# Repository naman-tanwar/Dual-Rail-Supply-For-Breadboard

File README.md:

# Dual-Rail-Supply-For-Breadboard
A Breadboard attachable Dual Rail power supply.
This circuit will provide +V, GND, and -V to the breadboard which is very useful for testing OP-AMP circuits. You can power this circuit with a 12V DC Jack and Micro USB Cable!
The Output voltage can be adjusted using the potentiometer provided. The max output voltage is around 27V (+13.5V and -13.5V). The Display shows the total output voltage.

# Project Image

# Circuit

# PCB

# 3D View

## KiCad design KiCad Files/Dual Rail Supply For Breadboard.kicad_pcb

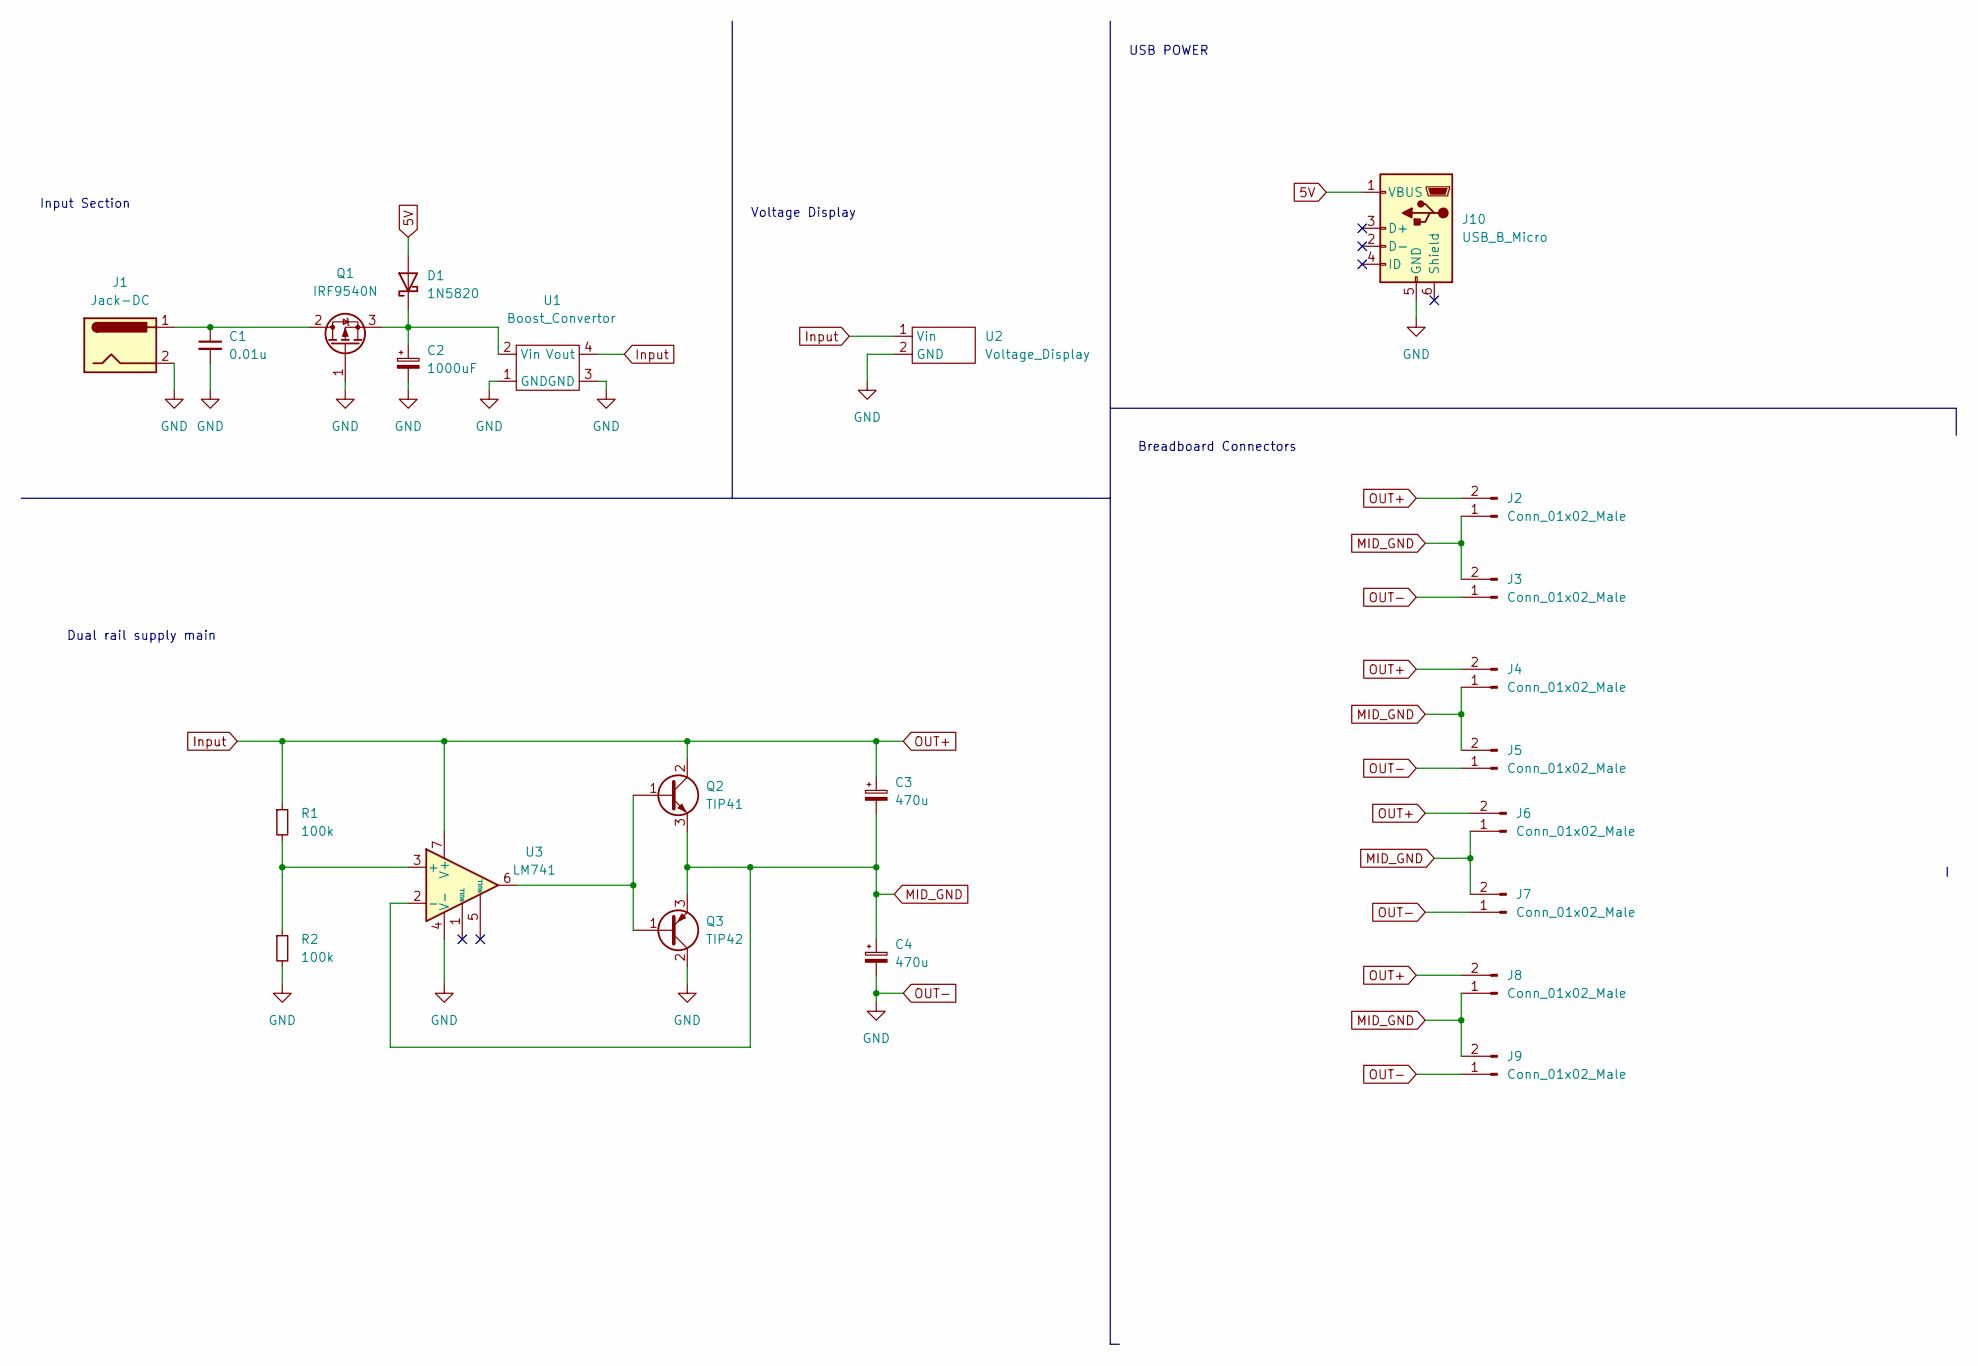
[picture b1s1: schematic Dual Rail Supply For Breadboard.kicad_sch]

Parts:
C1: 0.01u; C_Disc_D5.0mm_W2.5mm_P2.50mm
C2: 1000uF; CP_Radial_D12.5mm_P5.00mm
C3, C4: 470u; CP_Radial_D10.0mm_P5.00mm
D1: 1N5820; D_DO-201AD_P12.70mm_Horizontal
J1: Jack-DC; BarrelJack_Horizontal
J2, J3, J4, J5, J6, J7, J8, J9: Conn_01x02_Male; custom_PinHeader_1x02_P2.54mm_Vertical
J10: USB_B_Micro; USB_Micro-B_GCT_USB3076-30-A
Q1: IRF9540N; TO-220-3_Vertical
Q2: TIP41; TO-220-3_Vertical
Q3: TIP42; TO-220-3_Vertical
R1, R2: 100k; R_Axial_DIN0309_L9.0mm_D3.2mm_P12.70mm_Horizontal
U1: Boost_Convertor; MT3608 boost
U2: Voltage_Display; Voltage_disp_2wire
U3: LM741; DIP-8_W7.62mm_Socket_LongPads

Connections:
5V: D1.2 (A), J10.1 (VBUS)
Input: C3.1, J2.2, J4.2, J6.2, J8.2, Q2.2 (C), R1.1, U1.4 (Vout), U2.1 (Vin), U3.7 (V+)
MID_GND: C3.2, C4.1, J2.1, J3.2, J4.1, J5.2, J6.1, J7.2, J8.1, J9.2, Q2.3 (E), Q3.3 (E), U3.2 (-)
unnamed: C1.1, J1.1, Q1.2 (D)
unnamed: C2.1, D1.1 (K), Q1.3 (S), U1.2 (Vin)
unnamed: Q2.1 (B), Q3.1 (B), U3.6
unnamed: R1.2, R2.1, U3.3 (+)
OUT-: C1.2, C2.2, C4.2, J1.2, J3.1, J5.1, J7.1, J9.1, J10.5 (GND), Q1.1 (G), Q3.2 (C), R2.2, U1.1 (GND), U1.3 (GND), U2.2 (GND), U3.4 (V-)

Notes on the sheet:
Input Section
Dual rail supply main
Voltage Display
USB POWER
Breadboard Connectors

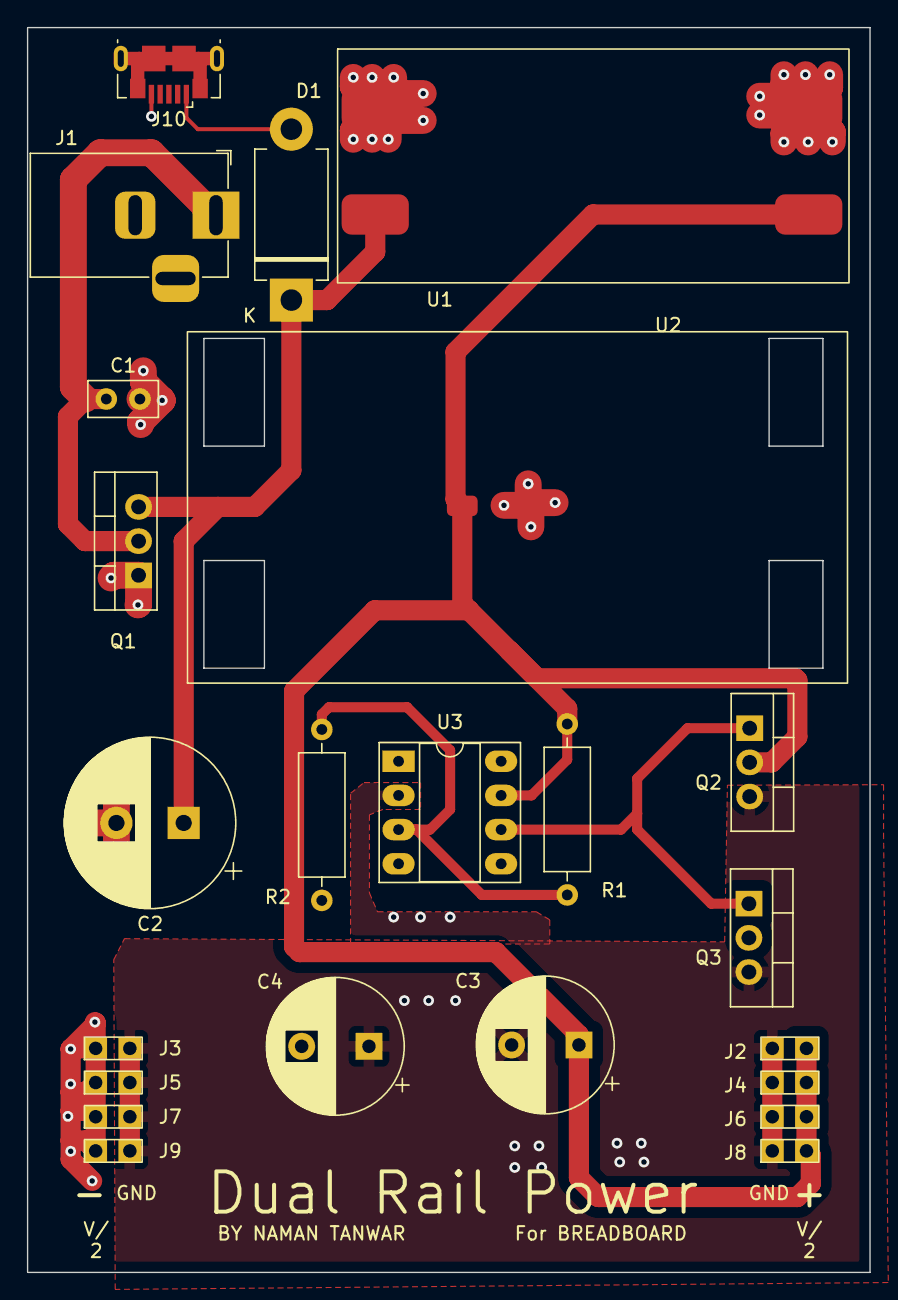
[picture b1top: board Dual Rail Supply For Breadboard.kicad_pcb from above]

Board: 2 copper layers, 62.6 x 92.5 mm, 23 parts (0 on the bottom side), 8 nets.
